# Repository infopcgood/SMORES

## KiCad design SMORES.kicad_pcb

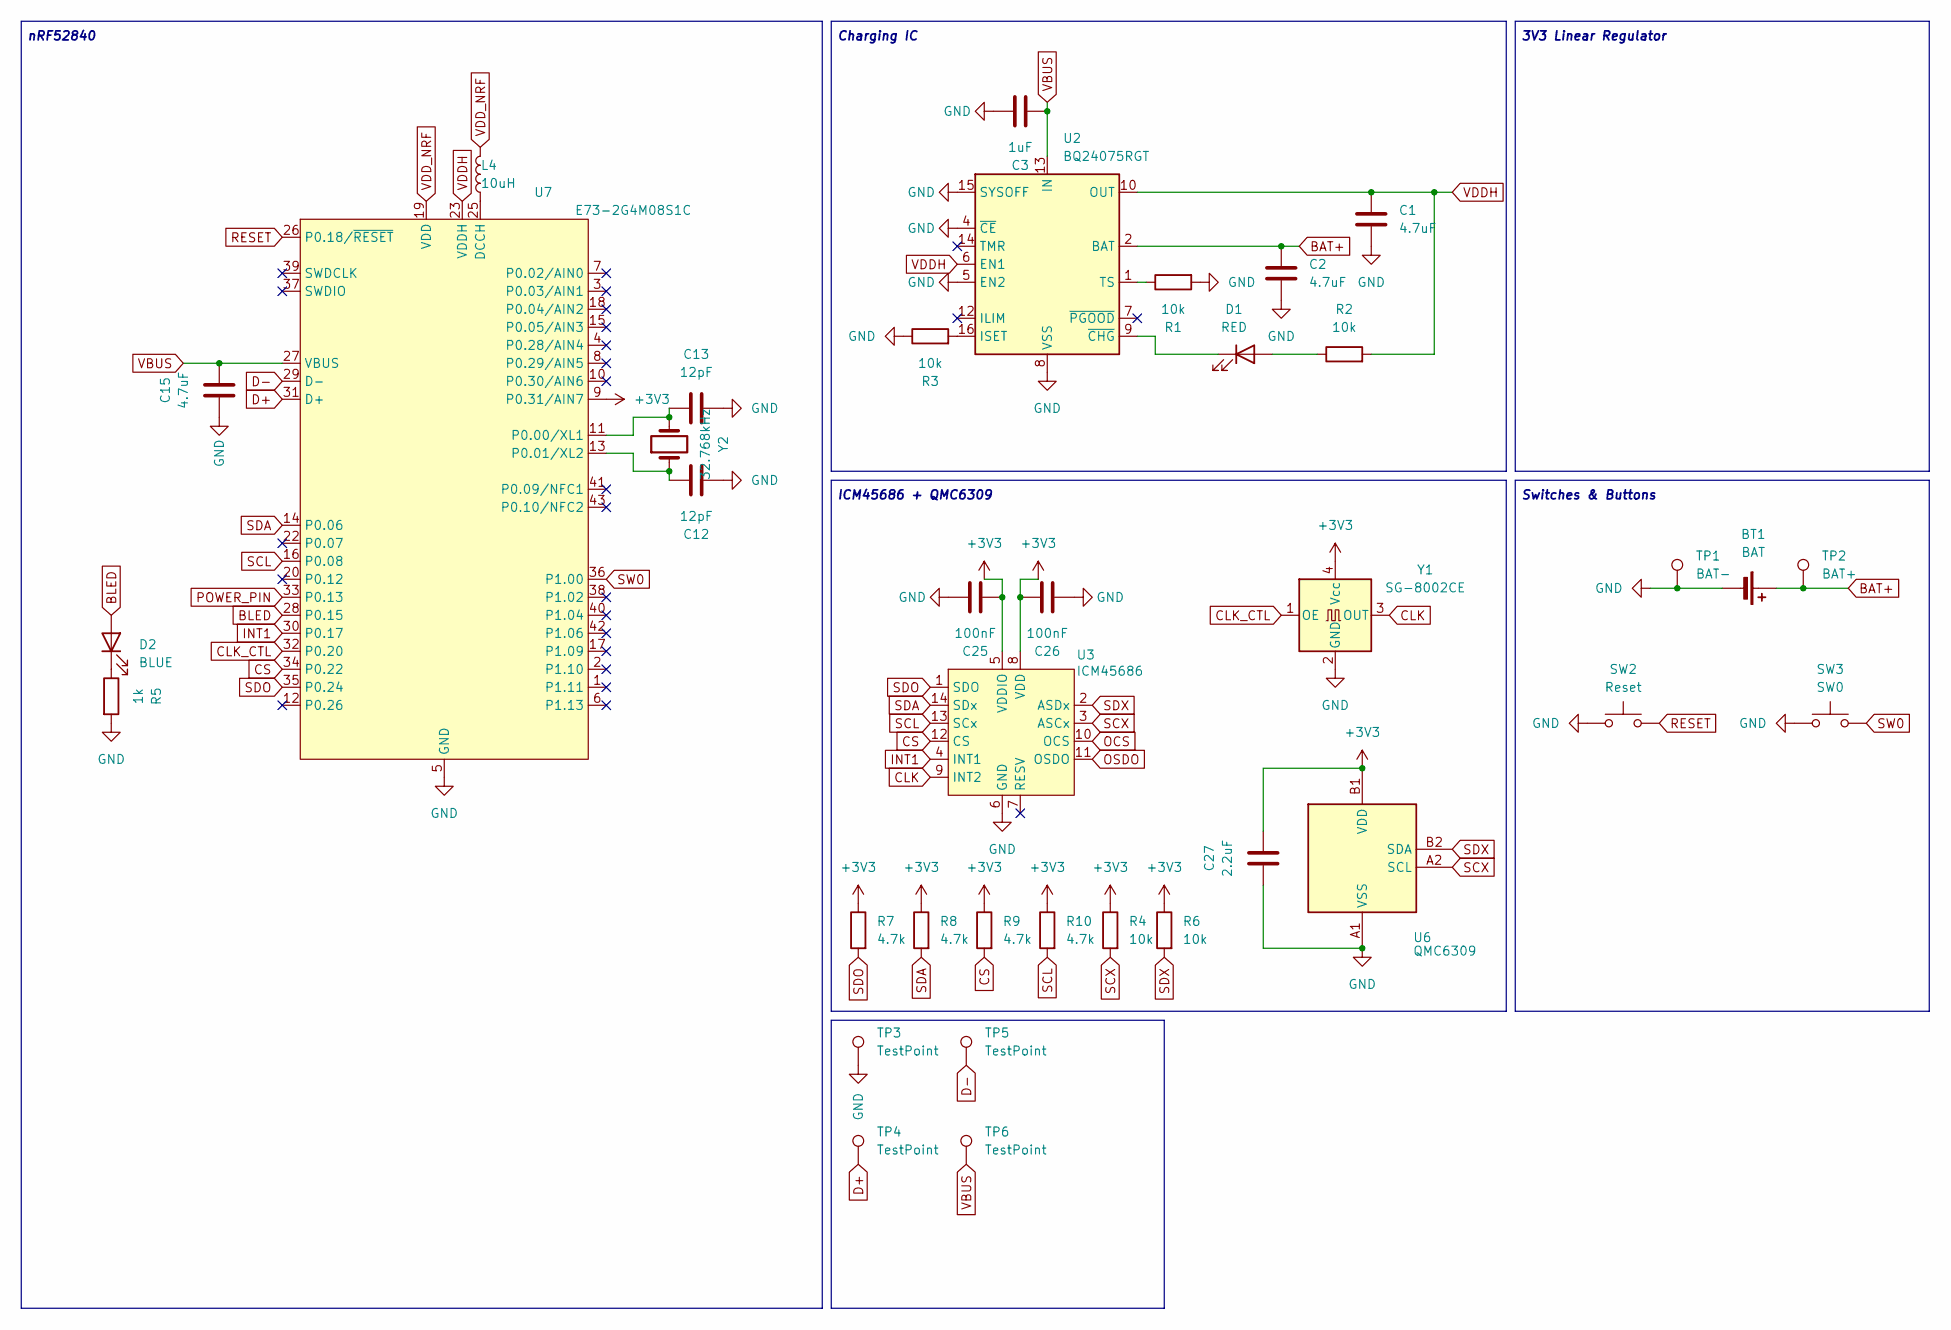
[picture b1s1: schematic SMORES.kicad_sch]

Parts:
BT1: BAT; Molex_PicoBlade_53048-0210_1x02_P1.25mm_Horizontal
C1, C2, C15: 4.7uF; C_0402_1005Metric
C3: 1uF; C_0402_1005Metric
C12, C13: 12pF; C_0603_1608Metric_Pad1.08x0.95mm_HandSolder
C25, C26: 100nF; C_0402_1005Metric
C27: 2.2uF; C_0402_1005Metric
D1: RED; LED_0603_1608Metric
D2: BLUE; LED_0603_1608Metric
L4: 10uH; L_0603_1608Metric_Pad1.05x0.95mm_HandSolder
R1, R2, R3, R4, R6: 10k; R_0402_1005Metric
R5: 1k; R_0402_1005Metric
R7, R8, R9, R10: 4.7k; R_0402_1005Metric
SW2: Reset; SW_TS-1088-AR02016
SW3: SW0; SW_TS-1088-AR02016
TP1: BAT-; TestPoint_Pad_D2.0mm
TP2: BAT+; TestPoint_Pad_D2.0mm
TP3, TP4, TP5, TP6: TestPoint; TestPoint_Pad_D1.5mm
U2: BQ24075RGT; VQFN-16-1EP_3x3mm_P0.5mm_EP1.6x1.6mm
U3: ICM45686; IC_ICM-45686
U6: QMC6309; IC_QMC6309
U7: E73-2G4M08S1C; LCSC C356849
Y1: SG-8002CE; Oscillator_SMD_SeikoEpson_SG8002CE-4Pin_3.2x2.5mm
Y2: 32.768kHz; Crystal_SMD_2012-2Pin_2.0x1.2mm

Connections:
+3V3: C25.2, C26.2, C27.1, R4.1, R6.1, R7.1, R8.1, R9.1, R10.1, U3.5 (VDDIO), U3.8 (VDD), U6.B1 (VDD), U7.9 (P0.31/AIN7), Y1.4 (Vcc)
BAT+: BT1.1 (+), C2.1, TP2.1, U2.2 (BAT), U2.3 (BAT)
BLED: D2.2 (A), U7.28 (P0.15)
CLK: U3.9 (INT2), Y1.3 (OUT)
CLK_CTL: U7.32 (P0.20), Y1.1 (OE)
CS: R9.2, U3.12 (CS), U7.34 (P0.22)
D+: TP4.1, U7.31 (D+)
D-: TP5.1, U7.29 (D-)
GND: BT1.2 (-), C1.2, C2.2, C3.2, C12.1, C13.1, C15.1, C25.1, C26.1, C27.2, R1.2, R3.1, R5.2, SW2.1, SW3.1, TP1.1, TP3.1, U2.4 (~CE), U2.5 (EN2), U2.8 (VSS), U2.15 (SYSOFF), U2.17 (VSS), U3.6 (GND), U6.A1 (VSS), U7.5 (GND), U7.21 (GND), U7.24 (GND), Y1.2 (GND)
INT1: U3.4 (INT1), U7.30 (P0.17)
unnamed: D1.2 (A), R2.1
unnamed: D1.1 (K), U2.9 (~CHG)
unnamed: D2.1 (K), R5.1
unnamed: R3.2, U2.16 (ISET)
unnamed: R1.1, U2.1 (TS)
unnamed: L4.1, U7.25 (DCCH)
unnamed: C13.2, U7.11 (P0.00/XL1), Y2.2
unnamed: C12.2, U7.13 (P0.01/XL2), Y2.1
OCS: U3.10 (OCS)
OSDO: U3.11 (OSDO)
POWER_PIN: U7.33 (P0.13)
RESET: SW2.2, U7.26 (P0.18/~RESET)
SCL: R10.2, U3.13 (SCx), U7.16 (P0.08)
SCX: R4.2, U3.3 (ASCx), U6.A2 (SCL)
SDA: R8.2, U3.14 (SDx), U7.14 (P0.06)
SDO: R7.2, U3.1 (SDO), U7.35 (P0.24)
SDX: R6.2, U3.2 (ASDx), U6.B2 (SDA)
SW0: SW3.2, U7.36 (P1.00)
VBUS: C3.1, C15.2, TP6.1, U2.13 (IN), U7.27 (VBUS)
VDDH: C1.1, R2.2, U2.6 (EN1), U2.10 (OUT), U2.11 (OUT), U7.23 (VDDH)
VDD_NRF: L4.2, U7.19 (VDD)

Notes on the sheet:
Charging IC
ICM45686 + QMC6309
Switches & Buttons
nRF52840
3V3 Linear Regulator

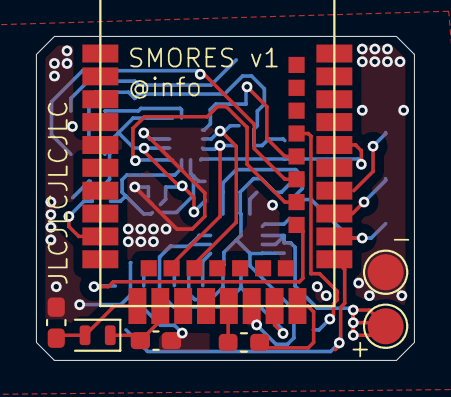
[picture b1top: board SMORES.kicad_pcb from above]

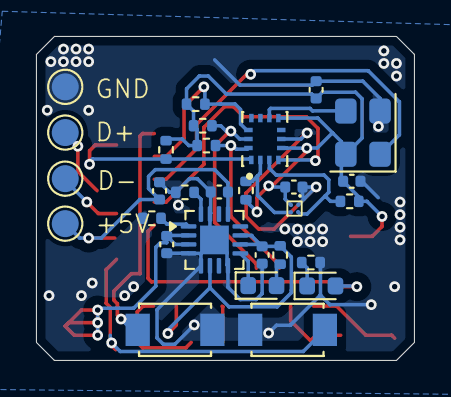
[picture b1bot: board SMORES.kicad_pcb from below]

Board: 2 copper layers, 21.0 x 18.0 mm, 36 parts (29 on the bottom side), 28 nets.

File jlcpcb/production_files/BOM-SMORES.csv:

Comment,Designator,Footprint,LCSC,Quantity
100nF,"C25,C26",C_0402_1005Metric,C6119799,2
10k,"R1,R2,R3,R4,R6",R_0402_1005Metric,C2906885,5
10uH,L4,L_0603_1608Metric_Pad1.05x0.95mm_HandSolder,C127280,1
12pF,"C12,C13",C_0603_1608Metric_Pad1.08x0.95mm_HandSolder,C363546,2
1k,R5,R_0402_1005Metric,C11702,1
1uF,C3,C_0402_1005Metric,C7503520,1
2.2uF,C27,C_0402_1005Metric,C7503516,1
32.768kHz,Y2,Crystal_SMD_2012-2Pin_2.0x1.2mm,C32346,1
4.7k,"R10,R7,R8,R9",R_0402_1005Metric,C3017492,4
4.7uF,"C1,C15,C2",C_0402_1005Metric,C307423,3
BLUE,D2,LED_0603_1608Metric,C2290,1
BQ24075RGT,U2,VQFN-16-1EP_3x3mm_P0.5mm_EP1.6x1.6mm,C15464,1
QMC6309,U6,IC_QMC6309,C5439871,1
RED,D1,LED_0603_1608Metric,C2286,1
Reset,SW2,SW_TS-1088-AR02016,C720477,1
SG-8002CE,Y1,Oscillator_SMD_SeikoEpson_SG8002CE-4Pin_3.2x2.5mm,C390506,1
SW0,SW3,SW_TS-1088-AR02016,C720477,1

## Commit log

2025-10-19 Add files
2025-11-30 Remove LDO and peripherals
2025-11-30 Redesign entire PCB and make it smaller
2025-11-30 Cleanup design and add silkscreen
